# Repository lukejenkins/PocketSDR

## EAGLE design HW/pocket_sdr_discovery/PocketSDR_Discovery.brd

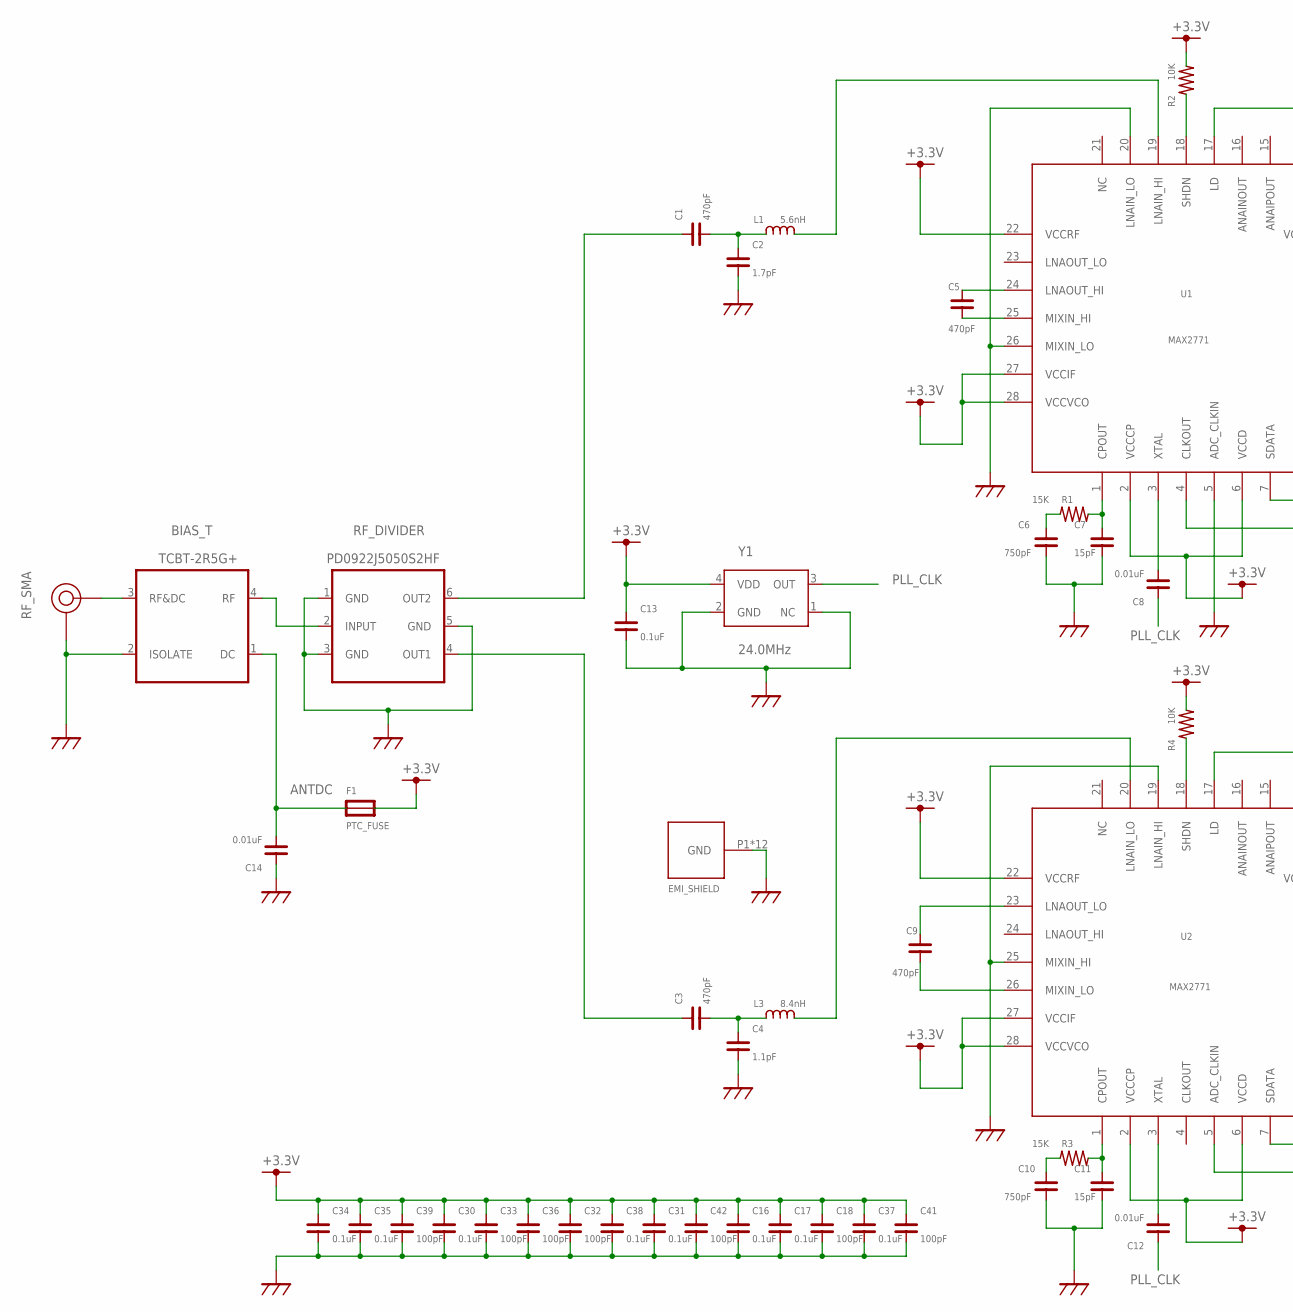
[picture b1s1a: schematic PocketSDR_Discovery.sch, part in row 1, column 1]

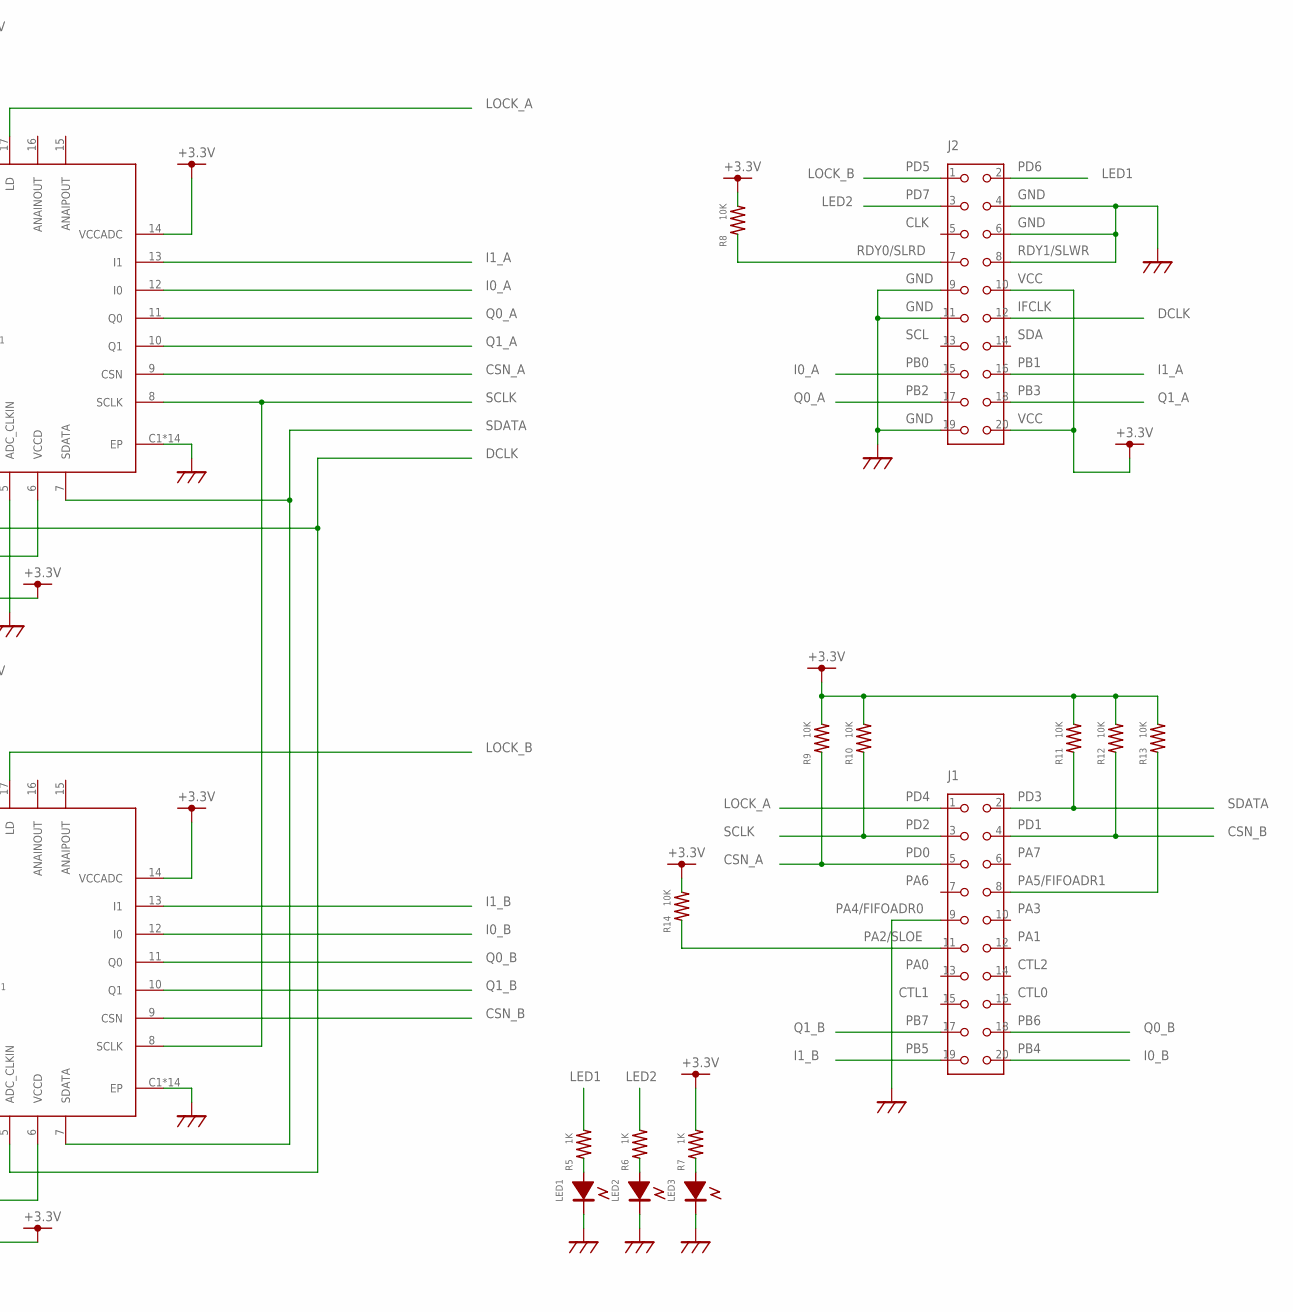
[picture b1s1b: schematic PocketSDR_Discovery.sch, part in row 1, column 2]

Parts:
BIAS_T: TCBT-2R5G+; BIAS_T
C1, C3, C5, C9: 470pF; C1005
C2: 1.7pF; C1005
C4: 1.1pF; C1005
C6, C10: 750pF; C1005
C7, C11: 15pF; C1005
C8, C12, C14: 0.01uF; C1005
C13, C16, C17, C30, C31, C34, C35, C37, C38: 0.1uF; C1005
C18, C32, C33, C36, C39, C41, C42: 100pF; C1005
F1: PTC_FUSE; C1608
J1, J2: PINH-2.54MM-20P
L1: 5.6nH; C1608
L3: 8.4nH; C1608
LED1, LED2, LED3: LED1608; LED_1608
R1, R3: 15K; C1005
R2, R4, R8, R9, R10, R11, R12, R13, R14: 10K; C1005
R5, R6, R7: 1K; C1005
RF-SHEILD-CASE: BMI-S-202-F BMI-S-202-C; BMI-S-202
RF_DIVIDER: PD0922J5050S2HF; RF_DIV
RF_SMA: SMA JACK EDGE MNT; SMA-ANG
U1, U2: MAX2771; TQFN28
Y1: 24.0MHz; TCXO2520

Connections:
+3.3V: C13.1, C16.1, C17.1, C18.1, C30.1, C31.1, C32.1, C33.1, C34.1, C35.1, C36.1, C37.1, C38.1, C39.1, C41.1, C42.1, F1.2, J2.10, J2.20, R2.2, R4.2, R7.2, R8.2, R9.2, R10.2, R11.2, R12.2, R13.2, R14.2, U1.2 (VCCCP), U1.6 (VCCD), U1.14 (VCCADC), U1.22 (VCCRF), U1.27 (VCCIF), U1.28 (VCCVCO), U2.2 (VCCCP), U2.6 (VCCD), U2.14 (VCCADC), U2.22 (VCCRF), U2.27 (VCCIF), U2.28 (VCCVCO), Y1.4 (VDD)
ANTDC: BIAS_T.1 (DC), C14.2, F1.1
CSN_A: J1.5, R9.1, U1.9 (CSN)
CSN_B: J1.4, R12.1, U2.9 (CSN)
DCLK: J2.12, U1.4 (CLKOUT), U2.5 (ADC_CLKIN)
FIFOADR1: J1.8, R13.1
GND: BIAS_T.2 (ISOLATE), C2.1, C4.2, C6.2, C7.2, C10.2, C11.2, C13.2, C14.1, C16.2, C17.2, C18.2, C30.2, C31.2, C32.2, C33.2, C34.2, C35.2, C36.2, C37.2, C38.2, C39.2, C41.2, C42.2, J1.9, J2.4, J2.6, J2.8, J2.9, J2.11, J2.19, LED1.2, LED2.2, LED3.2, RF-SHEILD-CASE.P1, RF-SHEILD-CASE.P2, RF-SHEILD-CASE.P3, RF-SHEILD-CASE.P4, RF-SHEILD-CASE.P5, RF-SHEILD-CASE.P6, RF-SHEILD-CASE.P7, RF-SHEILD-CASE.P8, RF-SHEILD-CASE.P9, RF-SHEILD-CASE.P10, RF-SHEILD-CASE.P11, RF-SHEILD-CASE.P12, RF_DIVIDER.1 (GND), RF_DIVIDER.3 (GND), RF_DIVIDER.5 (GND), RF_SMA.P2 (GND), RF_SMA.P3 (GND), RF_SMA.P4 (GND), RF_SMA.P5 (GND), U1.5 (ADC_CLKIN), U1.20 (LNAIN_LO), U1.26 (MIXIN_LO), U1.C1 (EP), U1.C2 (EP), U1.C3 (EP), U1.C4 (EP), U1.EP, U1.V1 (EP), U1.V2 (EP), U1.V3 (EP), U1.V4 (EP), U1.V5 (EP), U1.V6 (EP), U1.V7 (EP), U1.V8 (EP), U1.V9 (EP), U2.19 (LNAIN_HI), U2.25 (MIXIN_HI), U2.C1 (EP), U2.C2 (EP), U2.C3 (EP), U2.C4 (EP), U2.EP, U2.V1 (EP), U2.V2 (EP), U2.V3 (EP), U2.V4 (EP), U2.V5 (EP), U2.V6 (EP), U2.V7 (EP), U2.V8 (EP), U2.V9 (EP), Y1.1 (NC), Y1.2 (GND)
I0_A: J2.15, U1.12 (I0)
I0_B: J1.20, U2.12 (I0)
I1_A: J2.16, U1.13 (I1)
I1_B: J1.19, U2.13 (I1)
LED1: J2.2, R5.2
LED2: J2.3, R6.2
LOCK_A: J1.1, U1.17 (LD)
LOCK_B: J2.1, U2.17 (LD)
unnamed: C5.2, U1.25 (MIXIN_HI)
unnamed: C5.1, U1.24 (LNAOUT_HI)
unnamed: BIAS_T.3 (RF&DC), RF_SMA.P1 (RF)
unnamed: BIAS_T.4 (RF), RF_DIVIDER.2 (INPUT)
unnamed: LED3.1 (+), R7.1
unnamed: LED2.1 (+), R6.1
unnamed: LED1.1 (+), R5.1
unnamed: C1.2, C2.2, L1.1
unnamed: C8.2, U1.3 (XTAL)
unnamed: L1.2, U1.19 (LNAIN_HI)
unnamed: C1.1, RF_DIVIDER.6 (OUT2)
unnamed: C9.2, U2.26 (MIXIN_LO)
unnamed: C9.1, U2.23 (LNAOUT_LO)
unnamed: R2.1, U1.18 (SHDN)
unnamed: C7.1, R1.2, U1.1 (CPOUT)
unnamed: C6.1, R1.1
unnamed: C11.1, R3.2, U2.1 (CPOUT)
unnamed: C10.1, R3.1
unnamed: C3.1, RF_DIVIDER.4 (OUT1)
unnamed: C3.2, C4.1, L3.1
unnamed: L3.2, U2.20 (LNAIN_LO)
unnamed: R4.1, U2.18 (SHDN)
unnamed: C12.2, U2.3 (XTAL)
PLL_CLK: C8.1, C12.1, Y1.3 (OUT)
Q0_A: J2.17, U1.11 (Q0)
Q0_B: J1.18, U2.11 (Q0)
Q1_A: J2.18, U1.10 (Q1)
Q1_B: J1.17, U2.10 (Q1)
SCLK: J1.3, R10.1, U1.8 (SCLK), U2.8 (SCLK)
SDATA: J1.2, R11.1, U1.7 (SDATA), U2.7 (SDATA)
SLOE: J1.11, R14.1
SLRD: J2.7, R8.1

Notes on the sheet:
RDY1/SLWR
PD6
GND
VCC
IFCLK
SDA
PB1
PB3
PD5
PD7
CLK
RDY0/SLRD
SCL
PB0
PB2
PD4
PD2
PD0
PA6
PA4/FIFOADR0
PA2/SLOE
PA0
CTL1
PB7
PB5
PB4
PB6
CTL0
CTL2
PA1
PA3
PA5/FIFOADR1
PA7
PD1
PD3

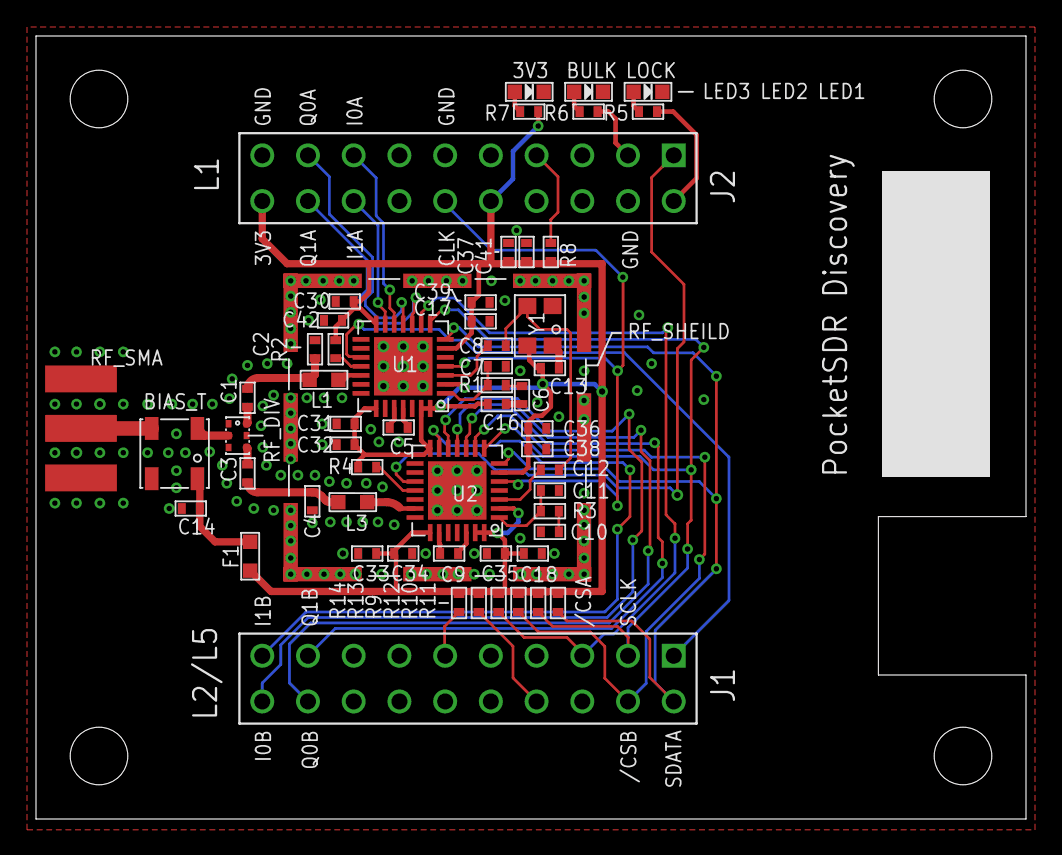
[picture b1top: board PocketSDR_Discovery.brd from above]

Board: 2 copper layers, 55.0 x 43.5 mm, 58 parts (0 on the bottom side), 47 nets.

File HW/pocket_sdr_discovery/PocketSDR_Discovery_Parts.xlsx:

No. | Value | Package | Parts | Distributor | Distributor Part# | Supplier | Supplier Part#
1 | 0.01uF | C1005 | C8, C12, C14 | Digi-Key | 478-1114-1-ND | Kyocera | 0402YC103KAT2A
2 | 0.1uF | C1005 | C13, C16, C17, C30, C31, C34, C35, C37, C38 | Digi-Key | 478-7888-1-ND | Kyocera | 0402YC104KAT2A
3 | 1.1pF | C1005 | C4 | Digi-Key | 311-3321-1-ND | YAGEO | CC0402BRNPO9BN1R1
4 | 1.7pF | C1005 | C2 | Digi-Key | 490-6074-1-ND | Murata | GJM1555C1H1R7BB01D
5 | 100pF | C1005 | C18, C32, C33, C36, C39, C41, C42 | Digi-Key | 478-1082-1-ND | Kyocera | 04025A101JAT2A
6 | 10k | R1005 | R2, R4, R8, R9, R10, R11, R12, R13, R14 | Digi-Key | 311-10KJRCT-ND | YAGEO | RC0402JR-0710KL
7 | 15k | R1005 | R1, R3 | Digi-Key | 311-15KJRCT-ND | YAGEO | RC0402JR-0715KL
8 | 15pF | C1005 | C7, C11 | Digi-Key | 478-1072-1-ND | Kyocera | 04025A150JAT2A
9 | 1k | R1005 | R5, R6, R7 | Digi-Key | 311-1.0KJRCT-ND | YAGEO | RC0402JR-071KL
10 | TCXO 24.0MHz | 2.5mmx2.0mm SMD | Y1 | Mouser | 732-TG252S24MCGNNM3 | Epson | TG2520SMN 24.0000M-MCGNNM3
11 | 470pF | C1005 | C1, C3, C5, C9 | Digi-Key | 478-1097-1-ND | Kyocera | 04025C471KAT2A
12 | 5.6nH | L1608 | L1 | Digi-Key | 490-1164-1-ND | Murata | LQW18AN5N6D00D
13 | 750pF | C1005 | C6, C10 | Digi-Key | 587-5098-1-ND | Taiyo Yuden | UMK105CH751JVHF
14 | 8.4nH | L1608 | L3 | Digi-Key | 490-15752-1-ND | Murata | LQW18AN8N4C8ZD
15 | LED Green | LED1608 | LED1, LED2, LED3 | Digi-Key | 754-1121-1-ND | Kingbright | APT1608SGC
16 | MAX2771 | TQFN28 | U1, U2 |  |  | Maxim | MAX2771ETI+
17 | RF_DIV | 2.04mm x 1.29mm SMD | RF_DIV | Digi-Key | 1173-1094-1-ND | Anaren | PD0922J5050S2HF
18 | PINH-20P | 2x10 pins, 2.54mm | J1, J2
19 | PTC_FUSE | F1608 | F1 | Digi-Key | 507-0ZCM0004FF2GCT-ND | Bel Fuse | 0ZCM0004FF2G
20 | SMA Jack | Edge Mount | RF_SMA | Digi-Key | CON-SMA-EDGE-S-ND | RF Solution | CON-SMA-EDGE-S
21 | Bias-T | 0.15" x 0.15" SMD | BIAS_T |  |  | Mini-Circuits | TCBT-2R5G+
22 | RF-SHEILD | 0.65" x 0.65" | RF_SHEILD | Digi-Key | 903-1051-1-ND | Laird | BMI-S-202-F
23 | RF-SHEILD-C | 0.668" x 0.668" |  | Digi-Key | 903-1014-ND | Laird | BMI-S-202-C

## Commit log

2021-12-27 Remove NO_RENUM option
2021-12-27 Daughter board for FX2LP Discovery Kit
2022-06-27 Add PocketSDR case and panel data
2022-11-13 Avoid rounding error in coffs
